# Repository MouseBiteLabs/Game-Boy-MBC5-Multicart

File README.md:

# Game Boy MBC5 Multicart

This is my design of a flashable MBC5-based multicart for the Game Boy. You can make a 2-in-1 or 4-in-1 cartridge, that changes games based on a button press or power cycling the Game Boy. With this board you can also make a single game, but with the addition of a pressable reset button on the cartridge.

The features are as follows:

- Able to make a cartridge with either 2x 2 MB games or 4x 1 MB games
- Adds a pressable button to the cartridge (no shell cutting required)
  - The button can be configured to cycle games on the cart, reset the console, or both
- Configurable to have separate save data for each game, or to share the same save data across multiple games
- Fully compatible with the <a href="https://www.gbxcart.com/">GBxCart RW</a> so you can transfer games and save files to and from the board

Some examples of fun cartridges you can make with this board are:
- A single Pokemon game that has a reset button
- Both Pokemon Red and Blue with separate saves
- Both Pokemon Red and Blue with *the same* save (save files are compatible between versions!)
- Both Pokemon Red and Blue with *the same* save that can switch between versions *during gameplay without resetting* (hotswap!)
- A single copy of Powerpuff Girls with two separate save files

All gerbers and source files can be found in this repo, as this project is fully open source. Technical documentation of the board can be found in the Technical folder.

## Tutorial Video

This is a video tutorial for the MBC3 multicart specifically, but the process is nearly identical.

")

## Important Things Before You Start

The most important thing to note is that SW2A MUST be in the OFF position. The board is still fully functional as long as you rely on the button inside the cartridge to switch games. **You cannot cycle games by turning the power on and off.** Details are below.

1) To use this board, you need to have an original Game Boy game that uses an MBC5 mapper chip. <a href="https://catskull.net/gb-rom-database/">You can find a list of games and their mappers here</a>. Use the search function. Please note the RAM is in bytes, not bits. Since SRAM in this repo is defined in bits, you need to convert by multiplying the number of bytes by 8.
2) You will need to remove the MBC5 from your donor cartridge for use on this board. This will require a hot air rework station or a hot plate. There's a list below of other parts you can re-use from the donor cartridge.
3) When soldering parts on, it's a good idea to put kapton tape or otherwise cover the bottom cartridge edge. You do not want to get solder on the cartridge contacts.
4) I am not responsible for any damage you do to your self or your property. Attempt this project at your own risk.
5) I do not guarantee design compatibility. You may encounter issues with certain games. There is also a chance I have made an error in the design or the BOM - if this is the case, I will do everything I can to address the problem as quickly as possible.
6) If you are using this board to make games other than for personal use, you must have permission from the originator to use and distribute any ROM images or other related material. You are responsible for making sure you adhere to any license requirements.

DO NOT use my circuit boards for profiting from stolen work - this especially includes homebrew content, ROM hacks, and using fan-made labels without permission from the originator. **Support original creators!**

## Board Characteristics and Order Information

The zipped folder contains all the gerber files for this board. The following options **must** be chosen when ordering boards for yourself.

- Thickness: 0.8mm
- Surface Finish: ENIG
- Gold Fingers: Yes, 30° chamfer

You can use the zipped folder at any board fabricator you like. You may also buy the board from PCBWay using this link (disclosure: I receive 10% of the sale value to go twoards future PCB orders of my own):

<a href="https://oshpark.com/shared_projects/hYLYPWZR">The board is also listed on OSH Park as well.</a> **Be sure to get them in 0.8mm thickness if you order from here.**

### Purchase from Etsy

I also offer the board on Etsy, if you would rather purchase through there - click the banner to be redirected.

## Required Equipment

The EEPROMs on the board needs to be programmed somehow. I recommend using the GBxCart, as mentioned. These boards are fully compatible with it, and it makes reflashing games extremely easy using <a href="https://github.com/lesserkuma/FlashGBX">lesserkuma's FlashGBX software</a>.

Alternatively, you can buy an EEPROM programmer with a TSOP adapter. The downside to this method is that you have to desolder the chip every time you want to program it. The <a href="https://flashcatusb.com/">FlashcatUSB</a> is one popular option in retro spaces.

## Battery Safety

When assembling a board, I recommend populating all the parts *except* the battery, and getting it to run initially without it. This is to make it easier to fix any solder connections that might need fixing, without having to worry about getting the battery hot. And if you need to rework anything near the battery after you've put it on the board, be safe and remove it before putting a hot soldering iron next to it.

And this should go without saying, but if you're assembling these boards with a hot plate or hot air, *do not* solder the battery on this way. You should use an iron, and keep heat off of the battery as much as possible. 

(Also check polarity!)

## Board Configurations

There's a lot to cover here. There are four separate switches to configure, and two different sizes of SRAM to pick from.

*Note that you can simply solder bridges from the middle pads of the switches to the left or right to the "ON" or "OFF" positions, instead of installing an actual switch.*

### SRAM Size Selection

There are two sizes of SRAM you can use, and the type you use will dictate how your save data is stored on the cartridge and if it's shared between games or not.

- If you use a 1 Mbit SRAM (like the AS6C1008), then each game you put on the cartridge will have its own separate save files. If you program multiple copies of the same game, then you can effectively have multiple save files on the same cart. Easy example is Pokemon games - they only let you have one save file, but if you put Pokemon Red on the multicart four times, then that gives you four separate save files!
- If you use a 256 Kbit SRAM (like the AS6C62256) then all the games you put on the cartridge will *share* the same RAM space.  This feature is probably only useful for Pokemon games. As an example: this means that if you made a cart that has Pokemon Red and Blue on it, you would play both versions with the same save data, as save data between the two games are compatible with each other.

### Game Cycling Mode Switch (SW2)

SW2, split into two separate switches SW2A (top half) and SW2B (bottom half), controls how you change games on the cartridge. The following table describes the different settings:

**DUE TO AN OVERLOOKED DATASHEET ERROR, SW2A *MUST* BE TURNED OFF. DO NOT USE IT IN THE "ON" POSITION.**

| Mode | SW2A (Bottom) | SW2B (Top) | Game change with reset? | Game change with button press? | Does the button reset? |
| ---- | ---------- | ------------- | ----------------------- | ------------------------------ | ---------------------- |
| 1    | OFF        | OFF           | No                      | Yes                            | Yes                    |
| 2    | OFF        | ON            | No                      | Yes                            | No                     |
|~~3~~ | ~~ON~~     | ~~OFF~~       | ~~Yes~~                 | ~~Yes~~                        | ~~Yes~~                |
|~~4~~ | ~~ON~~     | ~~ON~~        | ~~Yes~~                 | ~~No~~                         | ~~No~~                 |

The "game change" method in this table describes how you advance down the "game" columns described in the table for SW3.

### Game and Save Data Configuration Switch (SW3)

SW3, split into two separate switches SW3A (bottom half) and SW3B (top half), controls the order in which the ROM banks (the games) and the RAM banks (the save data) cycle. This table assumes you are using a 1 Mbit SRAM chip. If you are using a 256 Kbit SRAM, then every entry in the "RAM Banks" column can be described as "1x 256 Kbit", and all the "Game" columns will share that single RAM bank.

Please note that SW3A and SW3B are *different* than the SW3A and SW3B on the MBC3 Multicart PCB.

| Mode | SW3A (Top) | SW3B (Bottom) | ROM Banks  | RAM Banks   | Game 1     | Game 2     | Game 3     | Game 4     |
| ---- | ---- | ---- | ---------- | ----------- | ---------- | ---------- | ---------- | ---------- |
| A    | ON   | OFF  | 2x 2 MB    | 4x 256 Kbit | ROM1, RAM1 | ROM1, RAM2 | ROM2, RAM3 | ROM2, RAM4 |
| B    | OFF  | OFF  | 4x 1 MB    | 4x 256 Kbit | ROM1, RAM1 | ROM2, RAM2 | ROM3, RAM3 | ROM4, RAM4 |
| C    | ON   | ON   | 2x 2 MB    | 2x 256 Kbit | ROM1, RAM1 | ROM2, RAM2 |            |            |
| D    | OFF  | ON   | 2x 1 MB    | 2x 256 Kbit | ROM1, RAM1 | ROM2, RAM2 |            |            |

*Note: Mode D is useless. Just use Mode C instead.*

### Game Mode Examples

Here's a list of example cartridges you can make with these settings:
1) Pokemon Red, Blue, Yellow, and Green on one cartridge with separate save files that changes only via pressing the button, which also resets the game: **Mode 1B** with 1 Mbit SRAM
2) Pokemon Red and Blue with separate save files that changes by pressing the button *or* cycling power on the Game Boy: **Mode 3C** with 1 Mbit SRAM
3) Pokemon Red and Blue with the same save file that hotswaps when you press the button on the cartridge (changing games during gameplay): **Mode 2C** with 256 Kbit SRAM

## How to Program Games

When using the GBxCart to program multiple games to the cartridge, it's recommended to turn SW2A and SW2B to the OFF position. To change ROM/RAM banks to program, simply press the SW1 tactile button between programming steps. Using FlashGBX's "Refresh" button should show that the game information on the left of the screen changes after pressing the button.

If you're programming the flash chip separate from the board, you'll need to concatenate all the ROM files together into one large 4 MB file to program the chip with.

## Test Points and Final Checkout

On the back of the board are five test points. Here's where they are connected:

- TP1: SRAM supply voltage
- TP2: Battery voltage (after R1)
- TP3: Battery voltage (positive terminal of battery)
- TP4: Ground
- TP5: VCC input voltage

After you assemble your game, you should measure the current out of the battery. But first, you should program it with the GBxCart, or if you programmed the EEPROM separately, put it into a Game Boy and cycle power once. Then, flip the PCB upside down on a non-conductive surface (not your leg), and set your multimeter in DC millivolts (or volts). Put the positive probe on TP3 and the negative probe on TP2. If you used a 10kΩ for R1, as indicated in the BOM, you should read a voltage in the single or tens of millivolts. If you have something much higher, especially voltages above 100mV, then you likely have an issue or short circuit on the board somewhere.

**Note: You need to power up the game at least once before battery currents will make sense - the battery management ICs can start up in an unknown state before applying main power to the board.**

To estimate battery life, see <a href="https://github.com/MouseBiteLabs/Game-Boy-MBC5-Cartridge/tree/main/Technical#estimating-battery-life">this section in the MBC5 Technical Design Document</a>, or for more in-depth analysis, <a href="https://hackaday.io/project/11864-tritiled/log/72554-determining-maximum-runtime-176-to-202-years-cr2032">this Hackaday post</a>.

### Battery Size Considerations

The coin cells commonly used on Game Boy carts in order of increasing size are CR2016, CR2025, and CR2032. The CR2032 is the thickest, but yields the longest battery life.

Batteries that are as large as CR2032 will fit inside the shell, *however*, due to the thickness of the CR2032, using one makes it so the shell cannot be pressed down very easily. This makes the button inside the shell difficult to press reliably. For this reason, I recommend using the CR2025.

<a href="https://github.com/MouseBiteLabs/Game-Boy-MBC5-Cartridge/tree/main/Technical#estimating-battery-life">See this section in my main MBC5 repository for estimating battery life here.</a>

I haven't tested it, but I believe using battery holders instead of pre-tabbed batteries will similarly cause issues with trying to press the button in the middle of the cartridge.

### Why not FRAM?

This board is only suitable for using SRAM. One downside to SRAM, if you haven't figured it out yet, is that you need a battery to keep the SRAM powered on even when the game is turned off. So eventually the battery will die, and your save data is lost. Some people have used FRAM, or Ferroelectric RAM, to keep save data around even after the battery dies (specifically, the popular part that's used for FRAM carts is the FM18W08). But, using this FRAM chip has a handful of downsides, and the benefit of keeping save data after the battery dies *in my opinion* does not outweigh the cons, which are as follows:

1) Quality, new stock, 5V tolerant FRAM is expensive ($12+ per part).
2) Cheaper FRAM chips from eBay or Aliexpress are notoriously flaky (anecdotally, ~50% success rate).
3) FM18W08 maxes out at 256K (which is restrictive for multicarts).
4) FRAM memory access requires different chip select timing than SRAM, and the Game Boy expects SRAM, so it is not natively compatible with FRAM carts. The Gameboy Color specifically cannot (easily) be made to properly access FM18W08 chip. You *can* use an OR gate and add the CLK on the cart edge to try to achieve the necessary timing, but it only works (properly) for DMG/MGB/SGB, not the GBC. It usually *works* in practice for GBC, but it's technically a datasheet violation and can potentially cause issues in edge cases. <a href="https://github.com/Gekkio">(Thanks to gekkio for pointing this out!)</a>

Brand new SRAM chips are ~$3, and having the SRAM footprint also allows you to use SRAM from an original cart if desired. You will *easily* get more than a decade of life running on a battery. You're already assembling this cartridge; you can dump the save and replace the battery before then!

Note that this isn't to throw shade at any FRAM-based carts, but for me personally, it's more trouble than it's worth.

## Board Fitment

The shape of this board was originally meant to mimic original Game Boy circuit boards as closely as possible (v1.1 and earlier). Unfortunately, when placed in some aftermarket Game Boy cartridge shells (like those from Cloud Game Store), the circuit board has a lot of freedom to rotate around the main screw hole in the bottom-middle of the cartridge. This can cause misalignment when you put it in a Game Boy, which can cause a game to either not load properly (garbled Game Boy logo) or shut off the Game Boy because of a short circuit. This isn't *dangerous* or anything, just annoying.

In order to make the boards fit nicer in any kind of shell, for v1.4 I added extended tabs of circuit board material to the edges of the cartridges to keep it from rotating too much in shells, which was suggested to me by <a href="https://github.com/orangeglo">orangeglo</a>! (Thanks!)

If you're having trouble fitting the circuit board into a shell, because the tabs interfere with the cart edges, you can safely sand or trim them down as there is no copper within the tabs themselves. The only shell that appears to require any kind of trimming are Kitsch-Bent shells.

## Bill of Materials (BOM)

*Please note that there was an error in the published BOM before February 24, 2024. If you assembled your board before that date, I recommend you replace R5, R6, and C8 to their new values listed below.*

| Reference Designators | Value/Part Number      | Package        | Description        | Source                                           |
| --------------------- | ---------------------- | -------------- | ------------------ | ------------------------------------------------ |
| B1                    | CR2025, CR2016, CR2032*| See note above | Backup Battery     | [https://mou.sr/3PLccol](https://mou.sr/3PLccol) |
| C1                    | 0.1uF                  | 0603           | Capacitor (MLCC)   | [https://mou.sr/3ENc15O](https://mou.sr/3ENc15O) |
| C4                    | 0.1uF                  | 0603           | Capacitor (MLCC)   | [https://mou.sr/3ENc15O](https://mou.sr/3ENc15O) |
| C5                    | 0.1uF                  | 0603           | Capacitor (MLCC)   | [https://mou.sr/3ENc15O](https://mou.sr/3ENc15O) |
| C6                    | 10uF                   | 0603           | Capacitor (MLCC)   | [https://mou.sr/3mZtSkF](https://mou.sr/3mZtSkF) |
| C7                    | 0.1uF                  | 0603           | Capacitor (MLCC)   | [https://mou.sr/3ENc15O](https://mou.sr/3ENc15O) |
| C8                    | 0.01uF                 | 0603           | Capacitor (MLCC)   | [https://mou.sr/3AsRwK1](https://mou.sr/3AsRwK1) |
| C12                   | 0.1uF                  | 0603           | Capacitor (MLCC)   | [https://mou.sr/3ENc15O](https://mou.sr/3ENc15O) |
| Q1                    | 2N7002                 | SOT-23         | N-Channel FET      | [https://mou.sr/3rgfh6J](https://mou.sr/3rgfh6J) |
| R1                    | 10k                    | 0603           | Resistor           | [https://mou.sr/3riR7IH](https://mou.sr/3riR7IH) |
| R5                    | 130k                   | 0603           | Resistor           | [https://mou.sr/3MjXliy](https://mou.sr/3MjXliy) |
| R6                    | 130k                   | 0603           | Resistor           | [https://mou.sr/3MjXliy](https://mou.sr/3MjXliy) |
| R8                    | 10k                    | 0603           | Resistor           | [https://mou.sr/3riR7IH](https://mou.sr/3riR7IH) |
| R9                    | 130k                   | 0603           | Resistor           | [https://mou.sr/3MjXliy](https://mou.sr/3MjXliy) |
| R10                   | 49.9k                  | 0603           | Resistor           | [https://mou.sr/3Q3NRZO](https://mou.sr/3Q3NRZO) |
| SW1                   | See note               | 5.2 x 5.2mm    | Tactile Switch     | See Note |
| SW2                   | CAS-D20TA              | J Form Lead    | Dual SPDT          | [https://mou.sr/44YZNT5](https://mou.sr/44YZNT5) |
| SW3                   | CAS-D20TA              | J Form Lead    | Dual SPDT          | [https://mou.sr/44YZNT5](https://mou.sr/44YZNT5) |
| U1                    | 29F032, 29F033         | TSOP-40        | Flash EEPROM       | AliExpress or eBay                               |
| U2                    | MBC5                   | QFP-32         | MBC5 Mapper        | Donor MBC5 Game Boy cartridge                    |
| U3                    | AS6C62256, AS6C1008    | SOP-28, SOP-32 | SRAM               | [https://mou.sr/3sFegFF](https://mou.sr/3sFegFF) |
| U4                    | TPS3613                | MSOP-10        | Battery Management | [https://mou.sr/45Ir2kh](https://mou.sr/45Ir2kh) |
| U5                    | SN74HCS74              | TSSOP-14       | Dual Flip Flop     | [https://mou.sr/3QYGEuT](https://mou.sr/3QYGEuT) |
| U6                    | SN74AHC1G126           | SC70           | Tri-State Buffer   | [https://mou.sr/3T9Zdim](https://mou.sr/3T9Zdim) |
| U7                    | SN74AHC1G126           | SC70           | Tri-State Buffer   | [https://mou.sr/3T9Zdim](https://mou.sr/3T9Zdim) |
| U8                    | SN74AHC1G126           | SC70           | Tri-State Buffer   | [https://mou.sr/3T9Zdim](https://mou.sr/3T9Zdim) |

### Note about SW1

If SW1 is long enough, it will sit inside the shell in a way that lets you press it by lightly pressing on the cartridge shell. This way, you can activate it without removing it from the console. You need to find a switch that has an extended stem on AliExpress, eBay, or Amazon (**if you find a compatible switch on Mouser or Digikey, please let me know**). The measurements will be 5.2 mm x 5.2 mm, with a height of 3.5 mm. Sometimes these parts are listed as "4 mm x 4 mm" or "5 mm x 5 mm" instead. Check the datasheet, if available, to see if it'll fit the footprint. They should have listing pictures similar to the ones seen here:

### Note about SW2, SW3

Instead of using the somewhat pricey switch designated for SW2 and SW3, you can instead just bridge the pads with solder from the middle pad to the pad in the direction you want to set the switch to. For example - in the below picture, SW3A and SW3B are both in the "ON" position in both cases. (Note that the white switches on the right image are switched to the right.)

**REMINDER: SW2A MUST BE IN THE OFF POSITION.**

### Usable Donor Cartridge Parts

You can use a few parts from the donor cart on the new board to save some money. Note that you will generally get better reliability with new parts as opposed to old ones. For example: I have seen failed RAM chips from donors in the past.

1) **U2: MBC5** - This one is required [List of game compatible MBC5 to harvest](https://gbhwdb.gekkio.fi/cartridges/mbc5.html) or [this website by title of game name](https://catskull.net/gb-rom-database/)
2) **U3: SRAM** - You can use this part *only if* the sum of the RAM space for the games you're using is the same or less amount of RAM that the donor cartridge has. If you plan to have separate save data for every game, you'll probably need to buy an AS6C1008.

You could probably transfer over most of the 0.1uF capacitors but they're pretty cheap anyway, so I generally just recommend buying new resistors and capacitors.

## Things to Remember

- The 29F032 and 29F033 have been known to occasionally be defective upon arrival. They're either used, or new old stock, and usually only available from AliExpress.
- The footprint for the battery can fit a CR2032, CR2025, or CR2016 with solder tabs. The only difference is the mAh capacity (larger number = longer life). If you get Panasonic tabbed batteries, you may have to trim the battery tabs to make them fit on the footprint.
- Generally, ROM sizes are conveyed in terms of kilobytes and megabytes (KB, MB). RAM size is usually conveyed in terms of kilobits or megabits (Kbit, Mbit). You can convert Kbit and Mbit to KB and MB by dividing Kbit or Mbit by 8. For example, 256 Kbit = 32 KB.

## Labels

If you want a Bucket Mouse branded label for your cartridge, look no further than <a href="https://krizdingus.com/mousebitelabs/">krizdingus's designs</a>. Special thanks to Kris for designing these, they look awesome! (If you are going to order/print these, use the high-res images hosted on his website, and *keep the labels for personal or non-commercial use only.*)

## Why does SW2A need to be OFF?

SW2A in the ON position previously allowed the multicart to swap games whenever you power cycled the Game Boy. This was achieved by connecting the /RST line on the Game Boy to the CLK input on the flip-flop. The /RST line was held low when power was off by the RESET output of the TPS3613 battery management IC driving the gate of a FET.

The datasheet says this output is a push-pull output, and implies it will behave normally when power is off and the battery is being relied on for power. However, that is not the behavior I have later found to be true. Instead, if the voltage on the VDD pin is too low (like when the power is turned off), this RESET output floats. This causes the FET to not be asserted, and then allows the /RST line to float.

In Modes 3 or 4, where SW2A is in the ON position, /RST is connected to the flip-flop's CLK input. If /RST floats, then CLK floats, which can cause excess current draw from the flip-flop, draining the battery much faster than expected. Therefore, it is recommended to ONLY use a button to change games, and not to rely on power cycling.

A new board to replace this design with something more suitable will be completed in the future. In the meantime, *do not put SW2A in the ON position.*

## Revision History

### v1.3
- Fixed debounce circuit for push button
- Adjusted board edge tabs to better fit in shells

### v1.2
- Added nubs on the board edge to prevent the circuit board from rattling around in aftermarket cartridges

### v1.1
- Fix schematic errors
- Extended cart edge down by 0.25 mm for better fitment
- Added OSHW logo and "SUPPORT ORIGINAL CREATORS!"

### v1.0
- Prototype revision

## Resources and Acknowledgements

- <a href="http://www.devrs.com/gb/files/hardware.html">Jeff Frohwein's GameBoy Tech Page</a>
- <a href="https://gbhwdb.gekkio.fi/">Game Boy Hardware Database</a>
- <a href="https://catskull.net/gb-rom-database/">Nintendo Gameboy Game List</a>
- <a href="https://www.gbxcart.com/">insideGadgets discord server for GBxCart RW compatibility requirements</a>
- <a href="https://github.com/lesserkuma/FlashGBX">Lesserkuma's FlashGBX software</a>
- <a href="https://www.ti.com/lit/ds/symlink/tps3613-01.pdf?HQS=dis-mous-null-mousermode-dsf-pf-null-wwe&ts=1698238885366&ref_url=https%253A%252F%252Feu.mouser.com%252F">TPS3613 Datasheet</a>
- Board outline modified from <a href="https://tinkerer.us/projects/homebrew-gameboy-cartridge.html">Dillon Nichols's Homebrew Gameboy Cartridge project</a>
- Thanks to <a href="https://github.com/orangeglo">orangeglo</a> for his suggestion of adding spacers around the board edge for better fitment in aftermarket cartridges
- Some components from <a href="https://github.com/adafruit/Adafruit-Eagle-Library">Adafruit's Eagle parts library</a>
- Some components from <a href="https://www.snapeda.com/">SnapMagic</a>
- Thank you to <a href="https://github.com/Gekkio">gekkio</a> for their deep Game Boy knowledge resources, and for collaboration in demystifying some of the design choices on Game Boy cartridges
- Thanks to the awesome members of the <a href="https://moddedgameboy.club/">Modded Gameboy Club</a> for their feedback and support during the entire project development

## License

<br />This work is licensed under a <a rel="license" href="http://creativecommons.org/licenses/by-sa/4.0/">Creative Commons Attribution-ShareAlike 4.0 International License</a>. You are able to copy and redistribute the material in any medium or format, as well as remix, transform, or build upon the material for any purpose (even commercial) - but you **must** give appropriate credit, provide a link to the license, and indicate if any changes were made.

©MouseBiteLabs 2023

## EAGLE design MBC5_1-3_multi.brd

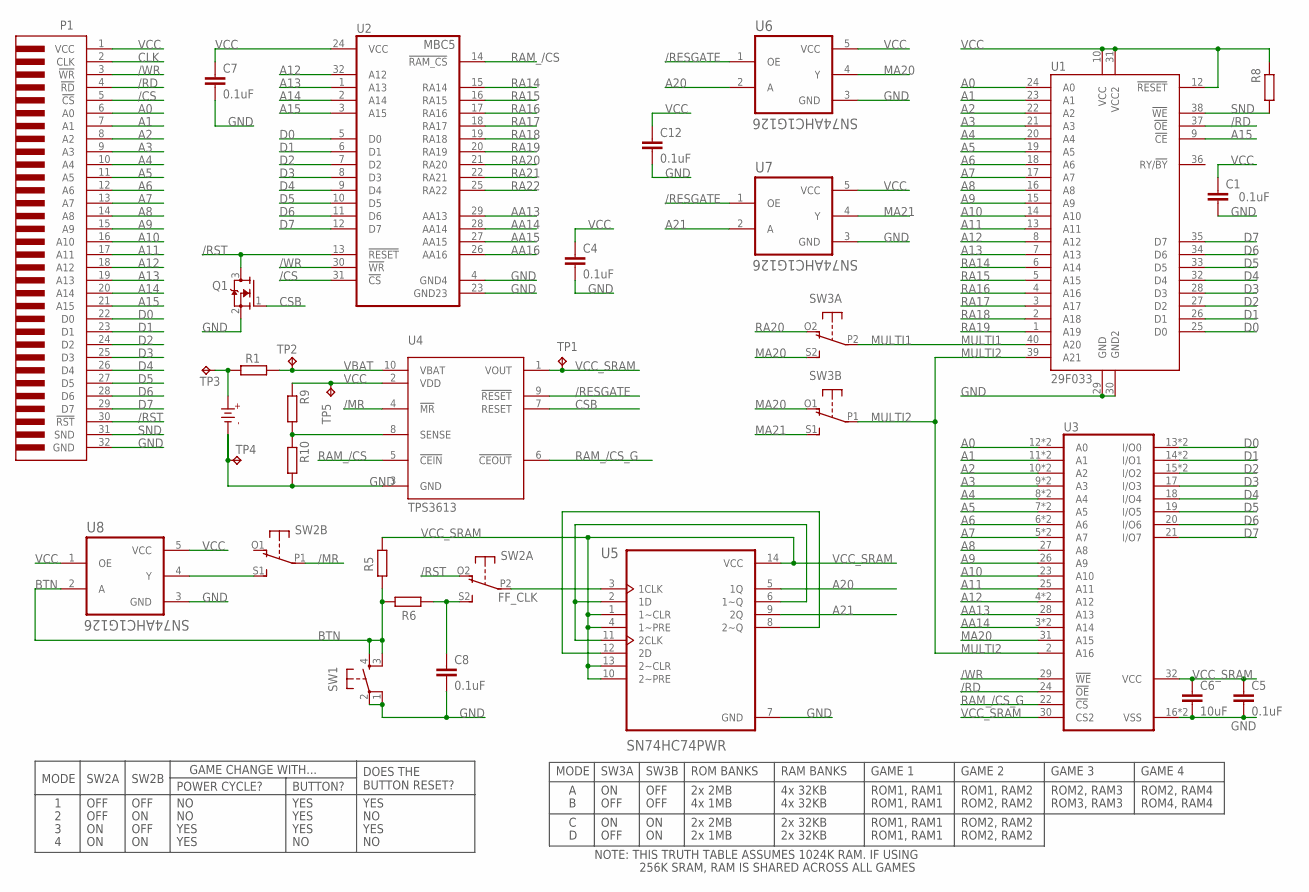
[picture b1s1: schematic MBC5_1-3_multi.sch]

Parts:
C1, C4, C5, C7, C8, C12: 0.1uF; C0603
C6: 10uF; C0603
P1: GBC_CARTTAB; GBC_CART_TABBED
Q1: 2N7002; SOT23
R1, R5, R6, R8, R9, R10: RR0603; R0603
SW1: SPST_TACT-KMR2; KMR2
SW2, SW3: SPDT-2S; CAS-D20A
TP1, TP2, TP3, TP4, TP5: TPB1,27; B1,27
U1: 29F033; TSOP-40
U2: MBC5; QFP-32
U3: 1008_62256_SRAM; SOP-32L
U4: TPS3613; MSOP-10
U5: SN74HC74PWR; SOP65P640X120-14N
U6, U7, U8: SN74AHC1G126; SC70
U$7: CR2025

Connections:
/CS: P1.5 (!CS), U2.31 (!CS)
/MR: SW2.P1, U4.4 (!MR)
/RD: P1.4 (!RD), U1.37 (!OE), U3.24 (!OE)
/RESGATE: U4.9 (!RESET), U6.1 (OE), U7.1 (OE)
/RST: P1.30 (!RST), Q1.3 (D), SW2.O2 (O), U2.13 (!RESET)
/WR: P1.3 (!WR), U2.30 (!WR), U3.29 (!WE)
A0: P1.6 (A0), U1.24 (A0), U3.12 (A0), U3.L12 (A0)
A1: P1.7 (A1), U1.23 (A1), U3.11 (A1), U3.L11 (A1)
A2: P1.8 (A2), U1.22 (A2), U3.10 (A2), U3.L10 (A2)
A3: P1.9 (A3), U1.21 (A3), U3.9 (A3), U3.L9 (A3)
A4: P1.10 (A4), U1.20 (A4), U3.8 (A4), U3.L8 (A4)
A5: P1.11 (A5), U1.19 (A5), U3.7 (A5), U3.L7 (A5)
A6: P1.12 (A6), U1.18 (A6), U3.6 (A6), U3.L6 (A6)
A7: P1.13 (A7), U1.17 (A7), U3.5 (A7), U3.L5 (A7)
A8: P1.14 (A8), U1.16 (A8), U3.27 (A8)
A9: P1.15 (A9), U1.15 (A9), U3.26 (A9)
A10: P1.16 (A10), U1.14 (A10), U3.23 (A10)
A11: P1.17 (A11), U1.13 (A11), U3.25 (A11)
A12: P1.18 (A12), U1.8 (A12), U2.32 (A12), U3.4 (A12), U3.L4 (A12)
A13: P1.19 (A13), U1.7 (A13), U2.1 (A13)
A14: P1.20 (A14), U2.2 (A14)
A15: P1.21 (A15), U1.9 (!CE), U2.3 (A15)
A20: U5.5 (1Q), U6.2 (A)
A21: U5.9 (2Q), U7.2 (A)
AA13: U2.29 (AA13), U3.28 (A13)
AA14: U2.28 (AA14), U3.3 (A14), U3.L3 (A14)
AA15: U2.27 (AA15)
AA16: U2.26 (AA16)
BTN: R5.2, R6.1, SW1.3 (S1), SW1.4 (S), U8.2 (A)
CLK: P1.2 (CLK)
CSB: Q1.1 (G), U4.7 (RESET)
D0: P1.22 (D0), U1.25 (D0), U2.5 (D0), U3.13 (I/O0), U3.L13 (I/O0)
D1: P1.23 (D1), U1.26 (D1), U2.6 (D1), U3.14 (I/O1), U3.L14 (I/O1)
D2: P1.24 (D2), U1.27 (D2), U2.7 (D2), U3.15 (I/O2), U3.L15 (I/O2)
D3: P1.25 (D3), U1.28 (D3), U2.8 (D3), U3.17 (I/O3)
D4: P1.26 (D4), U1.32 (D4), U2.9 (D4), U3.18 (I/O4)
D5: P1.27 (D5), U1.33 (D5), U2.10 (D5), U3.19 (I/O5)
D6: P1.28 (D6), U1.34 (D6), U2.11 (D6), U3.20 (I/O6)
D7: P1.29 (D7), U1.35 (D7), U2.12 (D7), U3.21 (I/O7)
FF_CLK: SW2.P2, U5.3 (1CLK)
GND: C1.2, C4.2, C5.2, C6.2, C7.2, C8.2, C12.2, P1.32 (GND), Q1.2 (S), R10.2, SW1.1, SW1.2, TP4.TP, U1.29 (GND), U1.30 (GND2), U2.4 (GND4), U2.23 (GND23), U3.16 (VSS), U3.L16 (VSS), U4.3 (GND), U5.7 (GND), U6.3 (GND), U7.3 (GND), U8.3 (GND), U$7.-
MA20: SW3.O1 (O), SW3.S2 (S), U3.31 (A15), U6.4 (Y)
MA21: SW3.S1 (S), U7.4 (Y)
MULTI1: SW3.P2, U1.40 (A20)
MULTI2: SW3.P1, U1.39 (A21), U3.2 (A16)
unnamed: SW2.S1 (S), U8.4 (Y)
unnamed: C8.1, R6.2, SW2.S2 (S)
unnamed: R1.2, TP3.TP, U$7.+
unnamed: U5.2 (1D), U5.6 (1~Q), U5.11 (2CLK)
unnamed: R9.2, R10.1, U4.8 (SENSE)
unnamed: U5.8 (2~Q), U5.12 (2D)
RA14: U1.6 (A14), U2.15 (RA14)
RA15: U1.5 (A15), U2.16 (RA15)
RA16: U1.4 (A16), U2.17 (RA16)
RA17: U1.3 (A17), U2.18 (RA17)
RA18: U1.2 (A18), U2.19 (RA18)
RA19: U1.1 (A19), U2.20 (RA19)
RA20: SW3.O2 (O), U2.21 (RA20)
RA21: U2.22 (RA21)
RA22: U2.25 (RA22)
RAM_/CS: U2.14 (!RAM_CS), U4.5 (!CEIN)
RAM_/CS_G: U3.22 (!CS), U4.6 (!CEOUT)
SND: P1.31 (SND), R8.2, U1.38 (!WE)
VBAT: R1.1, TP2.TP, U4.10 (VBAT)
VCC: C1.1, C4.1, C7.1, C12.1, P1.1 (VCC), R8.1, R9.1, TP5.TP, U1.10 (VCC), U1.12 (!RESET), U1.31 (VCC2), U2.24 (VCC), U4.2 (VDD), U6.5 (VCC), U7.5 (VCC), U8.1 (OE), U8.5 (VCC)
VCC_SRAM: C5.1, C6.1, R5.1, TP1.TP, U3.30 (CS2), U3.32 (VCC), U4.1 (VOUT), U5.1 (1~CLR), U5.4 (1~PRE), U5.10 (2~PRE), U5.13 (2~CLR), U5.14 (VCC)

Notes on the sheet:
SW3A
SW3B
OFF
ROM BANKS
RAM BANKS
4x 1MB
4x 32KB
2x 1MB
2x 2MB
2x 32KB
GAME 1
GAME 2
GAME 3
GAME 4
ROM1, RAM1
ROM2, RAM2
ROM3, RAM3
ROM4, RAM4
ROM1, RAM2
ROM2, RAM3
ROM2, RAM4
NOTE: THIS TRUTH TABLE ASSUMES 1024K RAM. IF USING
256K SRAM, RAM IS SHARED ACROSS ALL GAMES
MODE
SW2A
SW2B
POWER CYCLE?
DOES THE BUTTON RESET?
YES
BUTTON?
GAME CHANGE WITH...

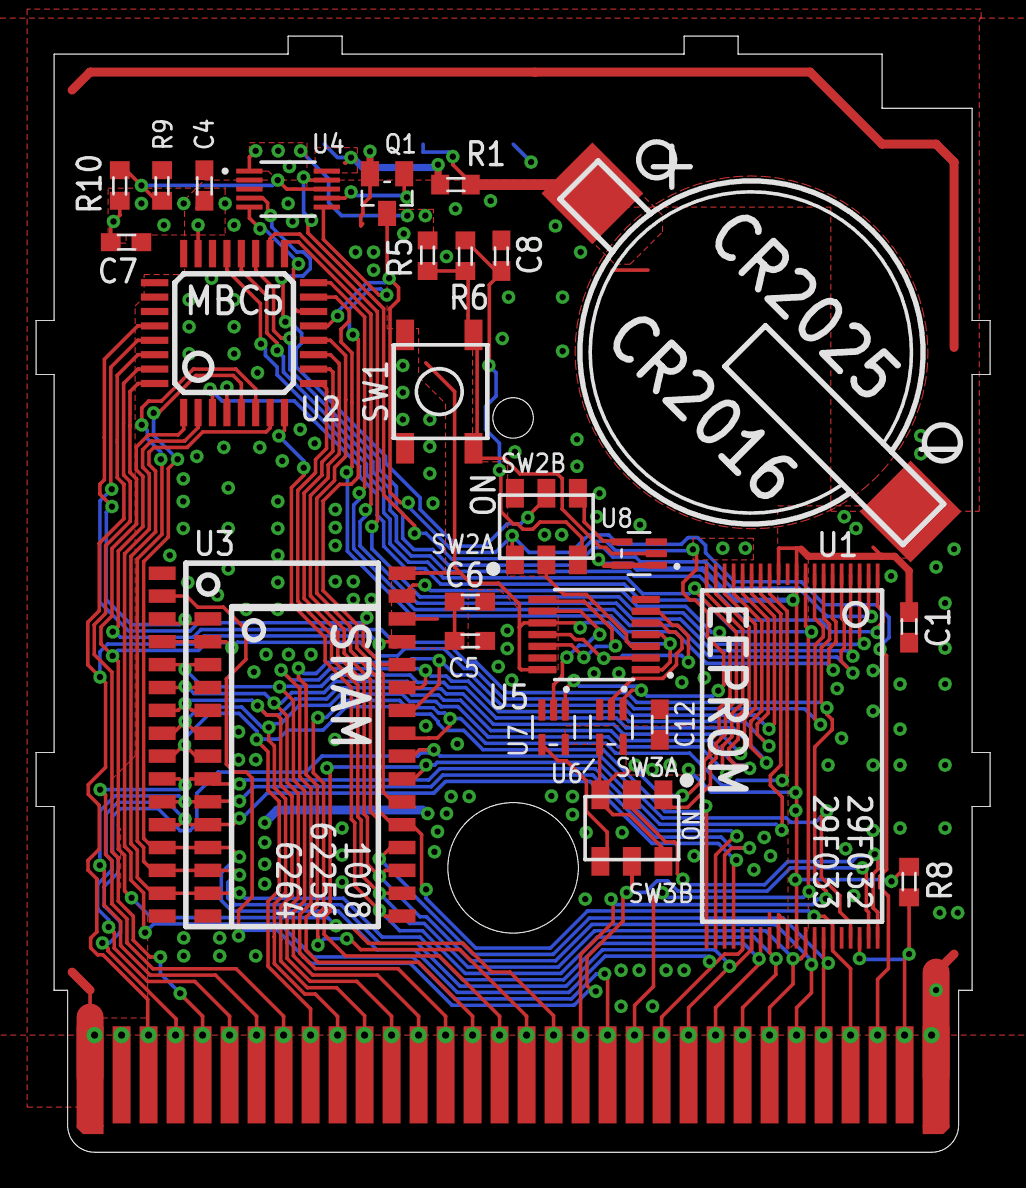
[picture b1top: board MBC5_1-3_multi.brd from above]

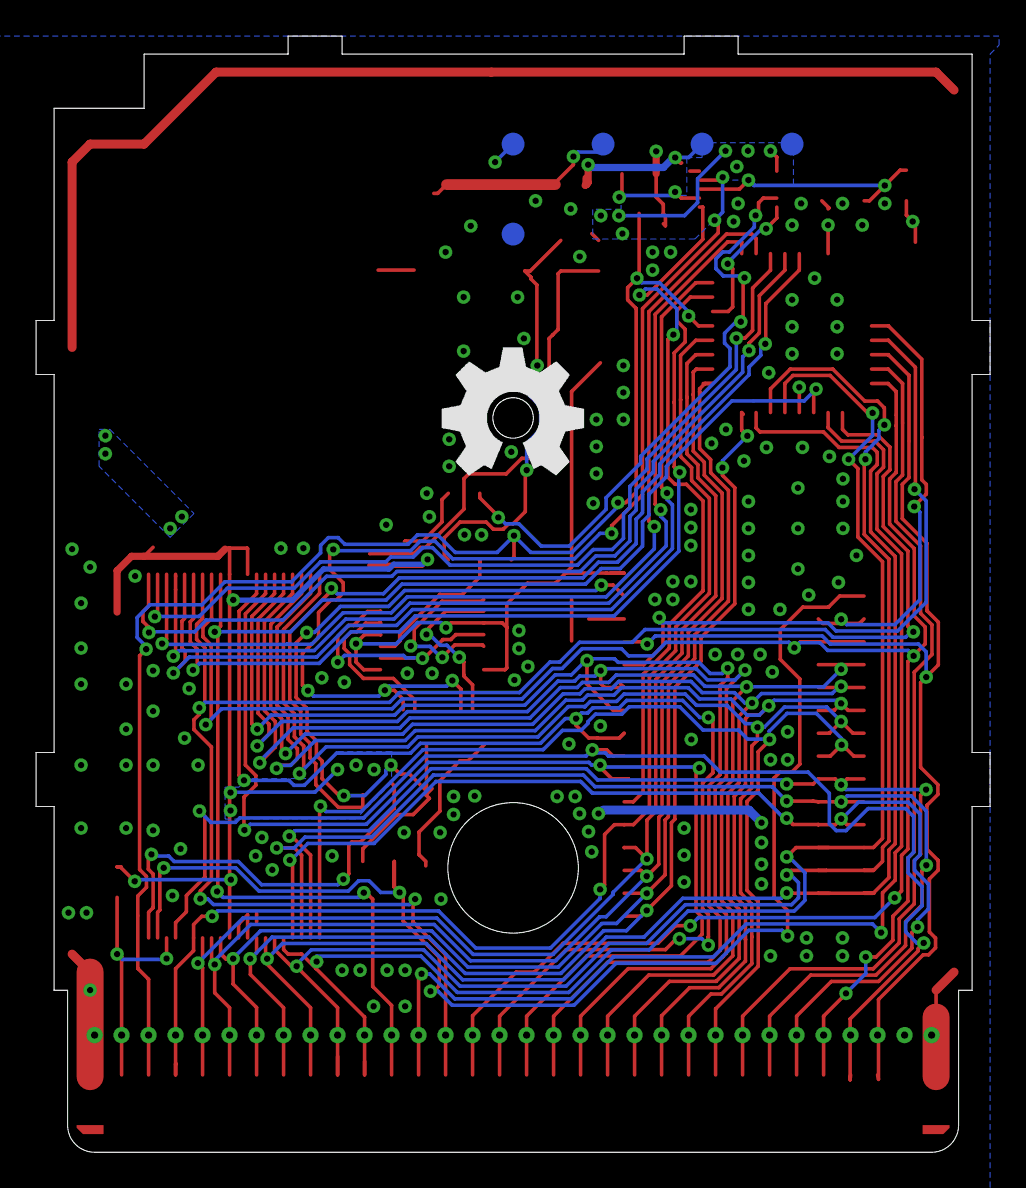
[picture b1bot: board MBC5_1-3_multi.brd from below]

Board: 2 copper layers, 53.0 x 62.0 mm, 32 parts (5 on the bottom side), 61 nets.

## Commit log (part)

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2024-07-05 Update README.md to add link for mbc5 cartridges
    Theses links could be good also for the MBC3
    [List of game compatible MBC5 to harvest](https://gbhwdb.gekkio.fi/cartridges/mbc5.html) or [this website by title of game name](https://catskull.net/gb-rom-database/)

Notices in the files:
README.md:
This work is licensed under a Creative Commons Attribution-ShareAlike 4.0 International License. You are able to copy and redistribute the material in any medium or format, as well as remix, transform, or build upon the material for any purpose (even commercial) - but you **must** give appropriate credit, provide a link t
©MouseBiteLabs 2023
